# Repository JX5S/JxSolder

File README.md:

# Do not order the board, or blindly copy the design, there are several known issues. Namely:
- USB-PD doesn't work. I thought I could do dead battery the way I did, but it's not a good way to do it, use PA9 and PA10 instead
- Display reset needs to be wired via an RC filter to 3.3V
- Vref needs to be connected up
- Button logic is flipped - so DFU firmware upload doesn't work
- There are unidirectional transils on the input - which blow up when incorrect polarity is plugged in. Should be replaced by bidirectional transils, the ideal diodes will protect the input
- There aren't dedicated I2C pullups, which limits speed

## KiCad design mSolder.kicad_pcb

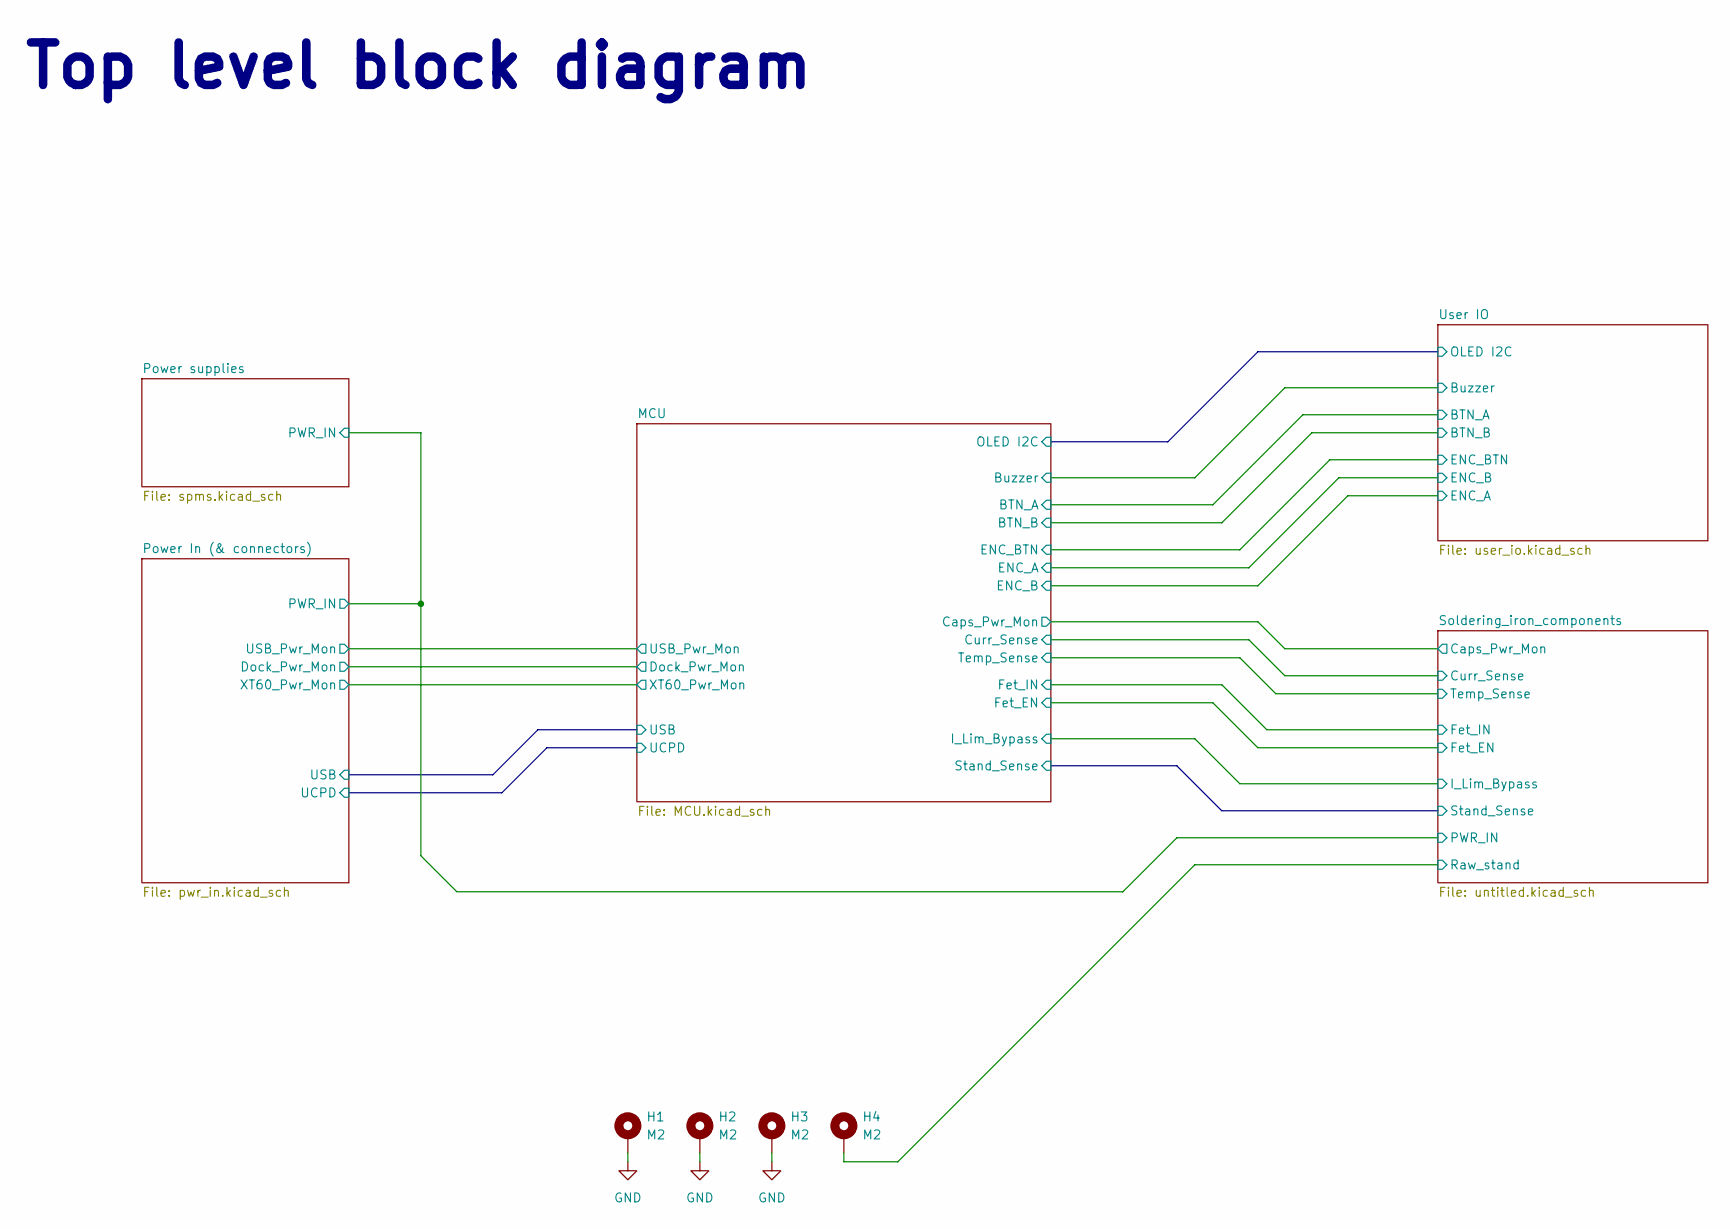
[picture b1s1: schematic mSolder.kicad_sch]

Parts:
H1, H2, H3, H4: M2; M2 solder nut; LCSC C3020134

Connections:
/Soldering_iron_components/Raw.Stand: H4.1; also elsewhere on the board
GND: H1.1, H2.1, H3.1; also elsewhere on the board

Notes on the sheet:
Top level block diagram

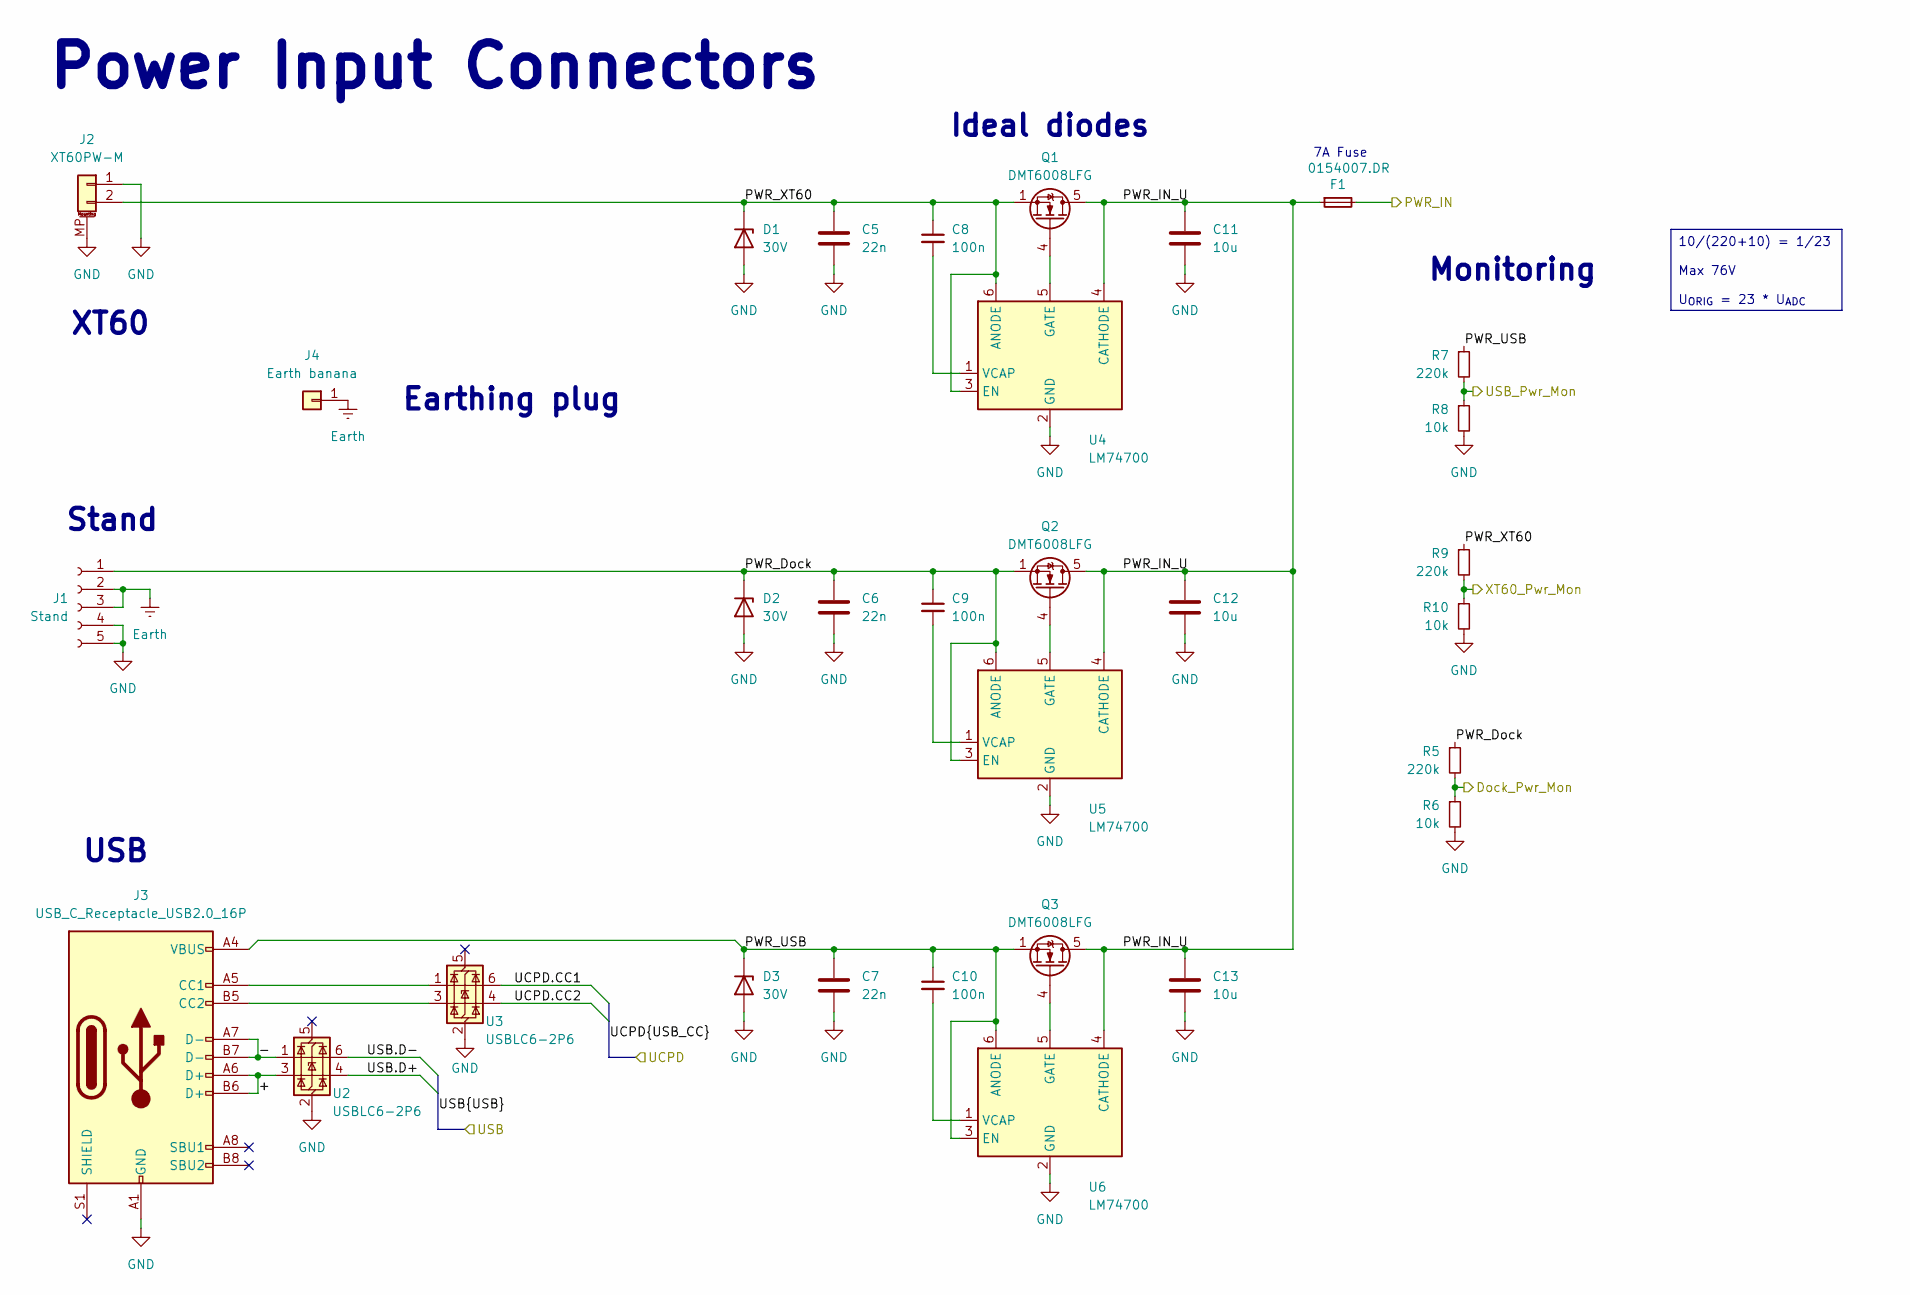
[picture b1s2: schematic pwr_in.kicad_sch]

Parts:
C5, C6, C7: 22n; C_0603_1608Metric; LCSC C21122
C8, C9, C10: 100n; C_0603_1608Metric; LCSC C1591
C11, C12, C13: 10u; C_1206_3216Metric; LCSC C13585
D1, D2, D3: 30V; D_SMA; LCSC C132943
F1: 0154007.DR; 0154100DR; Mouser Part Number 576-0154007.DR
J1: Stand; 1473969.1
J2: XT60PW-M; LCSC C98732
J3: USB_C_Receptacle_USB2.0_16P; USB_C_Receptacle_G-Switch_GT-USB-7010ASV; LCSC C963413
J4: Earth banana; CONN-TH_24.243.2; LCSC C7437324
Q1, Q2, Q3: DMT6008LFG; Diodes_PowerDI3333-8; LCSC C461111
R5, R7, R9: 220k; R_0603_1608Metric; LCSC C861231
R6, R8, R10: 10k; R_0603_1608Metric; LCSC C95204
U2, U3: USBLC6-2P6; SOT-666; LCSC C15999
U4, U5, U6: LM74700; SOT-23-6; LCSC C7589230

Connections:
/MCU/Dock_Pwr_Mon: R5.2, R6.1; also elsewhere on the board
/MCU/UCPD.CC1: U3.6 (I/O1); also elsewhere on the board
/MCU/UCPD.CC2: U3.4 (I/O2); also elsewhere on the board
/MCU/USB.D+: U2.4 (I/O2); also elsewhere on the board
/MCU/USB.D-: U2.6 (I/O1); also elsewhere on the board
/MCU/USB_Pwr_Mon: R7.2, R8.1; also elsewhere on the board
/MCU/XT60_Pwr_Mon: R9.2, R10.1; also elsewhere on the board
/Power In (& connectors)/+: J3.A6 (D+), J3.B6 (D+), U2.3 (I/O2)
/Power In (& connectors)/-: J3.A7 (D-), J3.B7 (D-), U2.1 (I/O1)
/Power In (& connectors)/PWR_Dock: C6.1, C9.1, D2.1 (K), J1.1, Q2.1 (S), Q2.2 (S), Q2.3 (S), R5.1, U5.3 (EN), U5.6 (ANODE)
/Power In (& connectors)/PWR_IN: F1.2; also elsewhere on the board
/Power In (& connectors)/PWR_IN_U: C11.1, C12.1, C13.1, F1.1, Q1.5 (D), Q2.5 (D), Q3.5 (D), U4.4 (CATHODE), U5.4 (CATHODE), U6.4 (CATHODE)
/Power In (& connectors)/PWR_USB: C7.1, C10.1, D3.1 (K), J3.A4 (VBUS), J3.A9 (VBUS), J3.B4 (VBUS), J3.B9 (VBUS), Q3.1 (S), Q3.2 (S), Q3.3 (S), R7.1, U6.3 (EN), U6.6 (ANODE)
/Power In (& connectors)/PWR_XT60: C5.1, C8.1, D1.1 (K), J2.2, Q1.1 (S), Q1.2 (S), Q1.3 (S), R9.1, U4.3 (EN), U4.6 (ANODE)
Earth: J1.2, J1.3, J4.1; also elsewhere on the board
GND: C5.2, C6.2, C7.2, C11.2, C12.2, C13.2, D1.2 (A), D2.2 (A), D3.2 (A), J1.4, J1.5, J2.1, J2.MP (MountPin), J3.A1 (GND), J3.A12 (GND), J3.B1 (GND), J3.B12 (GND), R6.2, R8.2, R10.2, U2.2 (GND), U3.2 (GND), U4.2 (GND), U5.2 (GND), U6.2 (GND); also elsewhere on the board
unnamed: J3.A5 (CC1), U3.1 (I/O1)
unnamed: J3.B5 (CC2), U3.3 (I/O2)
unnamed: Q1.4 (G), U4.5 (GATE)
unnamed: Q2.4 (G), U5.5 (GATE)
unnamed: Q3.4 (G), U6.5 (GATE)
unnamed: C8.2, U4.1 (VCAP)
unnamed: C9.2, U5.1 (VCAP)
unnamed: C10.2, U6.1 (VCAP)

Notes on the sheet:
Monitoring
Ideal diodes
Power Input Connectors
XT60
Earthing plug
USB
Stand
7A Fuse
10/(220+10) = 1/23 Max 76V U_{ORIG} = 23 * U_{ADC}

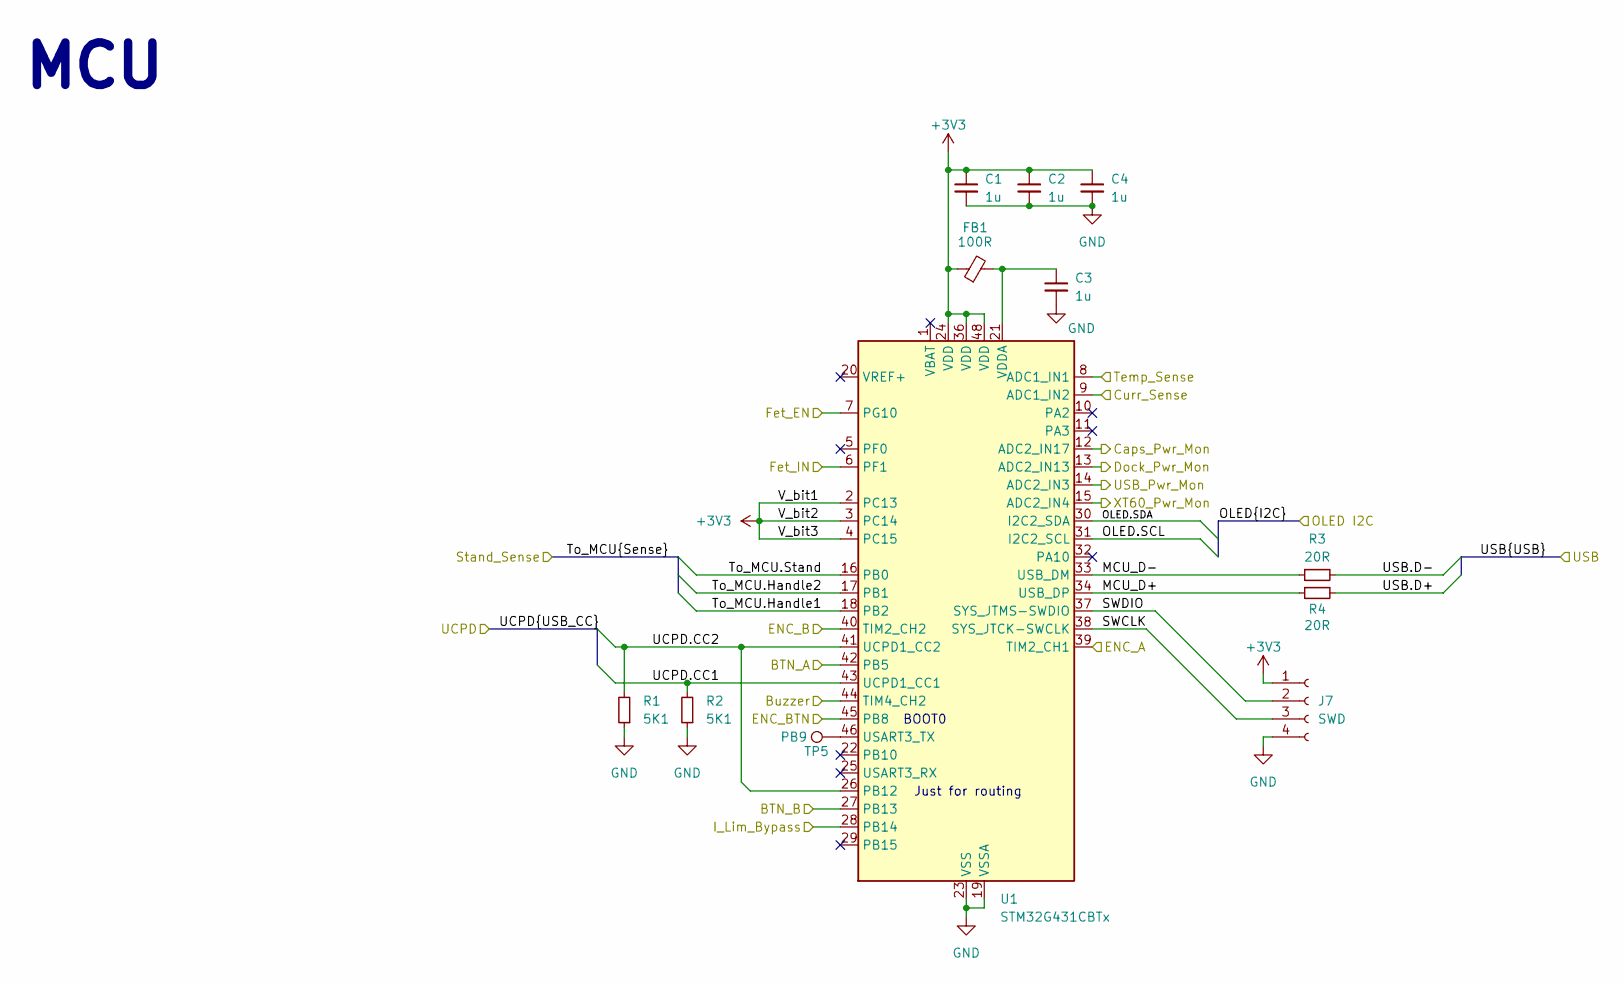
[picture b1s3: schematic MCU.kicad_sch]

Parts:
C1, C2, C3, C4: 1u; C_0603_1608Metric; LCSC C15849
FB1: 100R; R_0603_1608Metric; LCSC C107332
J7: SWD; PinHeader_1x04_P2.54mm_Vertical; LCSC C2691448
R1, R2: 5K1; R_0603_1608Metric; LCSC C105580
R3, R4: 20R; R_0603_1608Metric; LCSC C125758
TP5: PB9; TestPoint_Pad_D1.0mm
U1: STM32G431CBTx; LQFP-48_7x7mm_P0.5mm; LCSC C529355

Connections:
+3V3: C1.1, C2.1, C4.1, FB1.1, J7.1, U1.2 (PC13), U1.3 (PC14), U1.4 (PC15), U1.24 (VDD), U1.36 (VDD), U1.48 (VDD); also elsewhere on the board
/MCU/BTN_A: U1.42 (PB5); also elsewhere on the board
/MCU/BTN_B: U1.27 (PB13); also elsewhere on the board
/MCU/Buzzer: U1.44 (PB7); also elsewhere on the board
/MCU/Caps_Pwr_Mon: U1.12 (ADC2_IN17); also elsewhere on the board
/MCU/Curr_Sense: U1.9 (ADC1_IN2); also elsewhere on the board
/MCU/Dock_Pwr_Mon: U1.13 (ADC2_IN13); also elsewhere on the board
/MCU/ENC_A: U1.39 (TIM2_CH1); also elsewhere on the board
/MCU/ENC_B: U1.40 (TIM2_CH2); also elsewhere on the board
/MCU/ENC_BTN: U1.45 (PB8); also elsewhere on the board
/MCU/Fet_EN: U1.7 (PG10); also elsewhere on the board
/MCU/Fet_IN: U1.6 (PF1); also elsewhere on the board
/MCU/I_Lim_Bypass: U1.28 (PB14); also elsewhere on the board
/MCU/MCU_D+: R4.1, U1.34 (USB_DP)
/MCU/MCU_D-: R3.1, U1.33 (USB_DM)
/MCU/OLED.SCL: U1.31 (I2C2_SCL); also elsewhere on the board
/MCU/OLED.SDA: U1.30 (I2C2_SDA); also elsewhere on the board
/MCU/SWCLK: J7.3, U1.38 (SYS_JTCK-SWCLK)
/MCU/SWDIO: J7.2, U1.37 (SYS_JTMS-SWDIO)
/MCU/Temp_Sense: U1.8 (ADC1_IN1); also elsewhere on the board
/MCU/To_MCU.Handle1: U1.18 (PB2); also elsewhere on the board
/MCU/To_MCU.Handle2: U1.17 (PB1); also elsewhere on the board
/MCU/To_MCU.Stand: U1.16 (PB0); also elsewhere on the board
/MCU/UCPD.CC1: R2.2, U1.43 (UCPD1_CC1); also elsewhere on the board
/MCU/UCPD.CC2: R1.2, U1.26 (PB12), U1.41 (UCPD1_CC2); also elsewhere on the board
/MCU/USB.D+: R4.2; also elsewhere on the board
/MCU/USB.D-: R3.2; also elsewhere on the board
/MCU/USB_Pwr_Mon: U1.14 (ADC2_IN3); also elsewhere on the board
/MCU/XT60_Pwr_Mon: U1.15 (ADC2_IN4); also elsewhere on the board
GND: C1.2, C2.2, C3.2, C4.2, J7.4, R1.1, R2.1, U1.19 (VSSA), U1.23 (VSS), U1.35 (VSS), U1.47 (VSS); also elsewhere on the board
unnamed: TP5.1, U1.46 (USART3_TX)
unnamed: C3.1, FB1.2, U1.21 (VDDA)

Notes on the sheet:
BOOT0
Just for routing
MCU

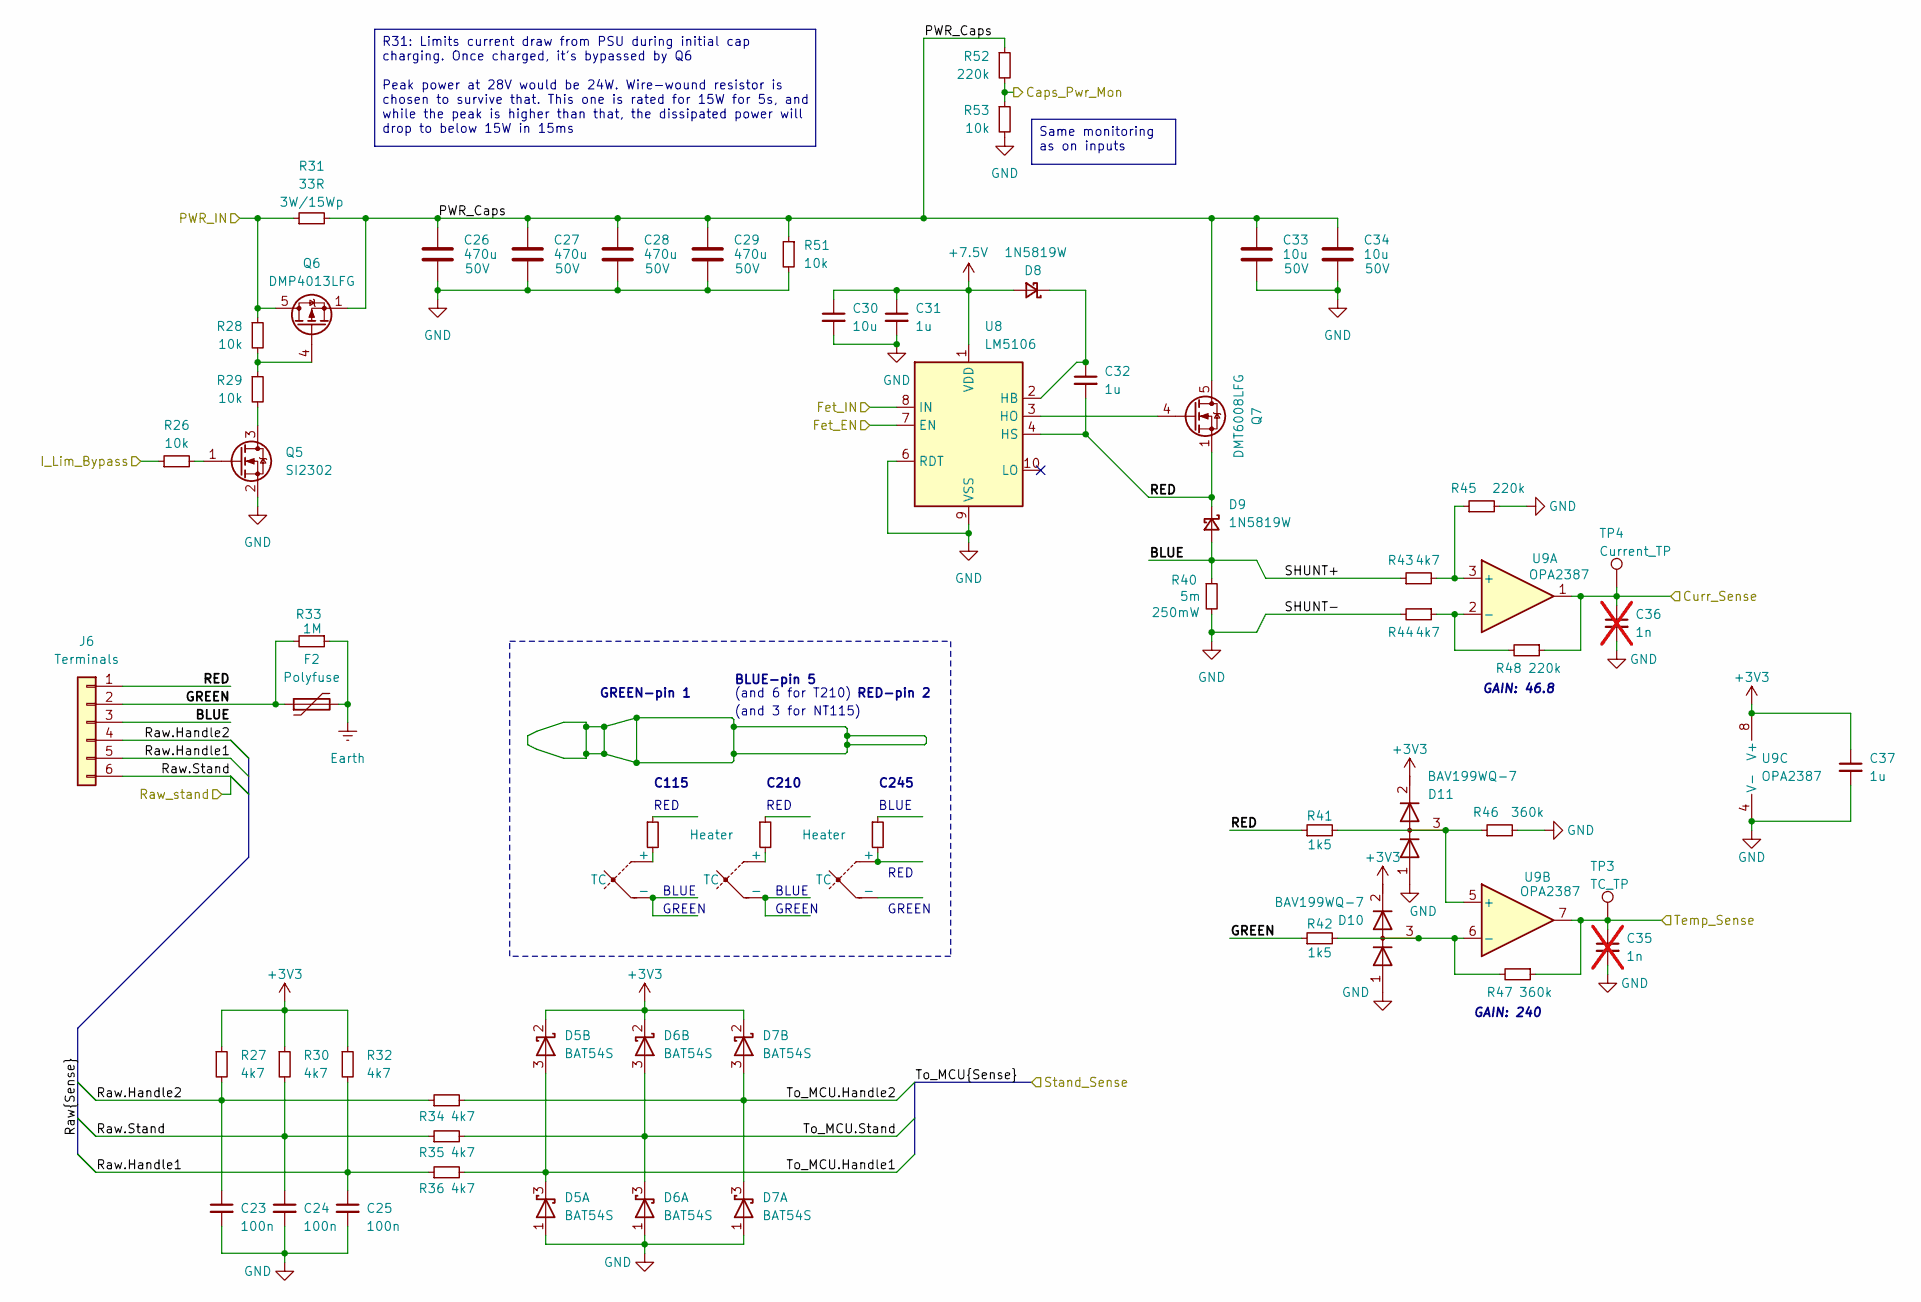
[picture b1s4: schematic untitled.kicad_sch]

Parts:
C23, C24, C25: 100n; C_0603_1608Metric; Manufacturer_Part_Number C0603C104J5RACTU; Mouser Part Number 80-C0603C104J5R
C26, C27, C28, C29: 470u; CP_Radial_D12.5mm_P5.00mm_L20_Laid on side; Voltage 50V; LCSC C1586027
C30: 10u; C_1206_3216Metric; LCSC C13585
C31, C32, C37: 1u; C_0603_1608Metric; LCSC C15849
C33, C34: 10u; C_1210_3225Metric; Voltage 50V; LCSC C126612
C35, C36: 1n; C_0603_1608Metric; Manufacturer_Part_Number C0603C102K3GAC; Mouser Part Number 80-C0603C102K3G; not fitted
D5, D6, D7: BAT54S; SOT-23; LCSC C47546
D8, D9: 1N5819W; D_SOD-123; LCSC C727115
D10, D11: BAV199WQ-7; SOT-323_SC-70; Mouser Part Number 621-BAV199WQ-7
F2: Polyfuse; Fuse_2512_6332Metric; LCSC C41364424
J6: Terminals; screw_terminal_6x3.81; LCSC C5143696
Q5: SI2302; TSOT-23; LCSC C5310967
Q6: DMP4013LFG; Diodes_PowerDI3333-8; LCSC C460203
Q7: DMT6008LFG; Diodes_PowerDI3333-8; LCSC C461111
R26, R28, R29, R51, R53: 10k; R_0603_1608Metric; LCSC C95204
R27, R30, R32, R34, R35, R36, R43, R44: 4k7; R_0603_1608Metric; Manufacturer_Part_Number ERJ-3RBD4701V; Mouser Part Number 667-ERJ-3RBD4701V
R31: 33R; R_TyOHM_SMW_3W; LCSC C2937341
R33: 1M; R_2512_6332Metric; LCSC C276335
R37, R38: Heater
R39: Heater 2 OHM
R40: 5m; R_1206_3216Metric; LCSC C875583
R41, R42: 1k5; R_0603_1608Metric; Manufacturer_Part_Number ERJ-H3ED1501V; Mouser Part Number 667-ERJ-H3ED1501V
R45, R48: 220k; R_0603_1608Metric; Manufacturer_Part_Number ERJ-3RED2203V; Mouser Part Number 667-ERJ-3RED2203V
R46, R47: 360k; R_0603_1608Metric; Manufacturer_Part_Number ERJ-3RED3603V; Mouser Part Number 667-ERJ-3RED3603V
R52: 220k; R_0603_1608Metric; LCSC C861231
TC1, TC2, TC3: TC
TP3: TC_TP; TestPoint_Pad_D1.0mm
TP4: Current_TP; TestPoint_Pad_D1.0mm
U8: LM5106; VSSOP-10_3x3mm_P0.5mm; LCSC C91879
U9: OPA2387; VSSOP-8_3x3mm_P0.65mm; LCSC C2861203

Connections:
+3V3: C37.1, D5.2 (K), D6.2 (K), D7.2 (K), D10.2, D11.2, R27.1, R30.1, R32.1, U9.8 (V+); also elsewhere on the board
+7.5V: C30.1, C31.1, D8.2 (A), U8.1 (VDD); also elsewhere on the board
/MCU/Caps_Pwr_Mon: R52.2, R53.1; also elsewhere on the board
/MCU/Curr_Sense: C36.1, R48.1, TP4.1, U9.1; also elsewhere on the board
/MCU/Fet_EN: U8.7 (EN); also elsewhere on the board
/MCU/Fet_IN: U8.8 (IN); also elsewhere on the board
/MCU/I_Lim_Bypass: R26.1; also elsewhere on the board
/MCU/Temp_Sense: C35.1, R47.1, TP3.1, U9.7; also elsewhere on the board
/MCU/To_MCU.Handle1: D5.3 (K), R36.2; also elsewhere on the board
/MCU/To_MCU.Handle2: D7.3 (K), R34.2; also elsewhere on the board
/MCU/To_MCU.Stand: D6.3 (K), R35.2; also elsewhere on the board
/Power In (& connectors)/PWR_IN: Q6.5 (D), R28.1, R31.1; also elsewhere on the board
/Soldering_iron_components/BLUE: D9.2 (A), J6.3, R40.1, R43.1
/Soldering_iron_components/GREEN: F2.1, J6.2, R33.2, R42.1
/Soldering_iron_components/PWR_Caps: C26.1, C27.1, C28.1, C29.1, C33.1, C34.1, Q6.1 (S), Q6.2 (S), Q6.3 (S), Q7.5 (D), R31.2, R51.1, R52.1
/Soldering_iron_components/RED: C32.2, D9.1 (K), J6.1, Q7.1 (S), Q7.2 (S), Q7.3 (S), R41.1, U8.4 (HS)
/Soldering_iron_components/Raw.Handle1: C25.1, J6.5, R32.2, R36.1
/Soldering_iron_components/Raw.Handle2: C23.1, J6.4, R27.2, R34.1
/Soldering_iron_components/Raw.Stand: C24.1, J6.6, R30.2, R35.1; also elsewhere on the board
Earth: F2.2, R33.1; also elsewhere on the board
GND: C23.2, C24.2, C25.2, C26.2, C27.2, C28.2, C29.2, C30.2, C31.2, C33.2, C34.2, C35.2, C36.2, C37.2, D5.1 (A), D6.1 (A), D7.1 (A), D10.1, D11.1, Q5.2 (S), R40.2, R44.2, R45.2, R46.2, R51.2, R53.2, U8.6 (RDT), U8.9 (VSS), U9.4 (V-); also elsewhere on the board
unnamed: C32.1, D8.1 (K), U8.2 (HB)
unnamed: Q5.3 (D), R29.2
unnamed: Q5.1 (G), R26.2
unnamed: Q6.4 (G), R28.2, R29.1
unnamed: Q7.4 (G), U8.3 (HO)
unnamed: R37.2, TC1.1 (+)
unnamed: R38.2, TC2.1 (+)
unnamed: R39.2, TC3.1 (+)
unnamed: R43.2, R45.1, U9.3 (+)
unnamed: R44.1, R48.2, U9.2 (-)
unnamed: D11.3, R41.2, R46.1, U9.5 (+)
unnamed: D10.3, R42.2, R47.2, U9.6 (-)

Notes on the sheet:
BLUE
RED-pin 2
BLUE-pin 5
C245
GREEN
(and 3 for NT115)
GAIN: 240
RED
GREEN-pin 1
RED
GAIN: 46.8
C210
C115
(and 6 for T210)
Same monitoring as on inputs
R31: Limits current draw from PSU during initial cap charging. Once charged, it's bypassed by Q6 Peak power at 28V would be 24W. Wire-wound resistor is chosen to survive that. This one is rated for 15W for 5s, and while the peak is higher than that, the dissipated power will drop to below 15W in 15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

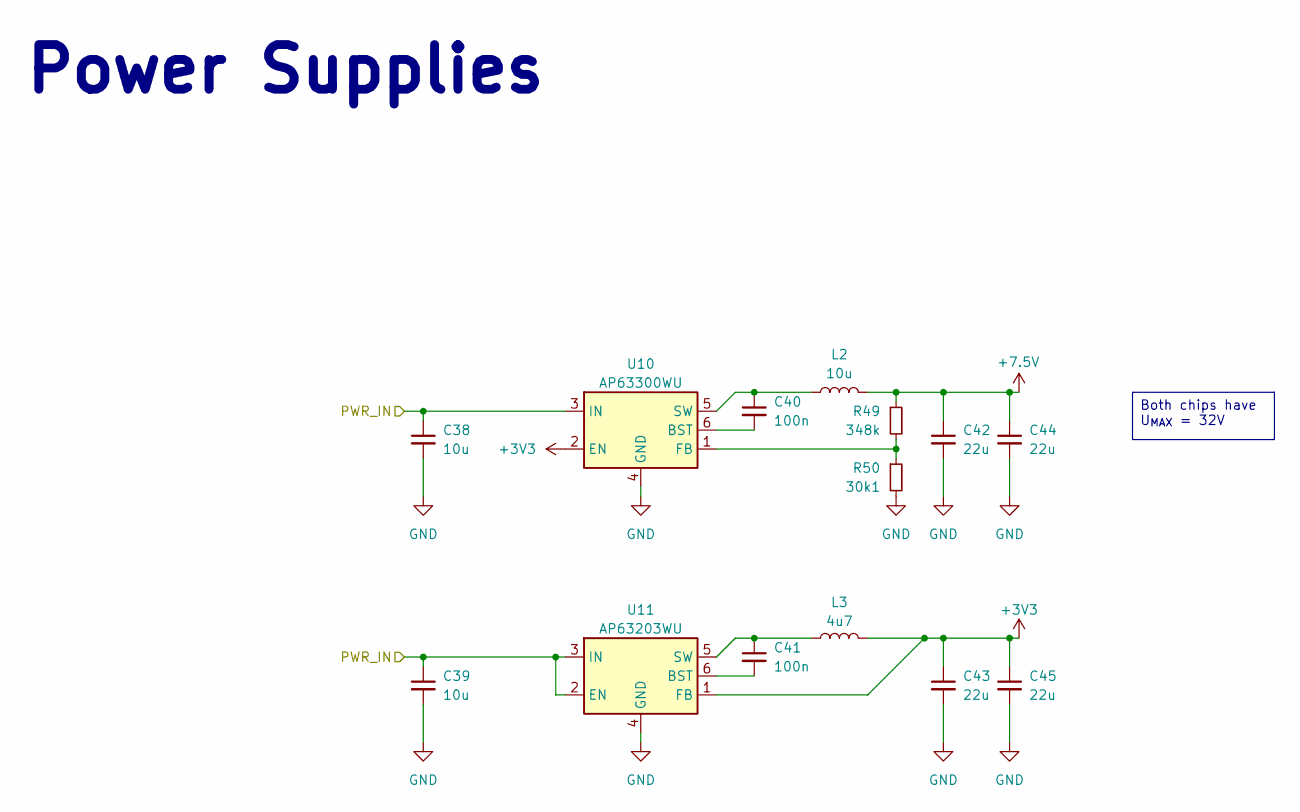
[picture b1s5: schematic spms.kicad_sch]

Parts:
C38, C39: 10u; C_1206_3216Metric; LCSC C13585
C40, C41: 100n; C_0603_1608Metric; LCSC C1591
C42, C43, C44, C45: 22u; C_1206_3216Metric; LCSC C77091
L2: 10u; L_Chilisin_BMRA00040420; LCSC C177242
L3: 4u7; L_Chilisin_BMRA00040420; LCSC C167208
R49: 348k; R_0603_1608Metric; LCSC C227828
R50: 30k1; R_0603_1608Metric; LCSC C137745
U10: AP63300WU; TSOT-23-6; LCSC C2158012
U11: AP63203WU; TSOT-23-6; LCSC C780769

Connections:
+3V3: C43.1, C45.1, L3.2, U10.2 (EN), U11.1 (FB); also elsewhere on the board
+7.5V: C42.1, C44.1, L2.2, R49.1; also elsewhere on the board
/Power In (& connectors)/PWR_IN: C38.1, C39.1, U10.3 (IN), U11.2 (EN), U11.3 (IN); also elsewhere on the board
GND: C38.2, C39.2, C42.2, C43.2, C44.2, C45.2, R50.2, U10.4 (GND), U11.4 (GND); also elsewhere on the board
unnamed: C40.2, U10.6 (BST)
unnamed: R49.2, R50.1, U10.1 (FB)
unnamed: C40.1, L2.1, U10.5 (SW)
unnamed: C41.2, U11.6 (BST)
unnamed: C41.1, L3.1, U11.5 (SW)

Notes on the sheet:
Power Supplies
Both chips have U_{MAX} = 32V

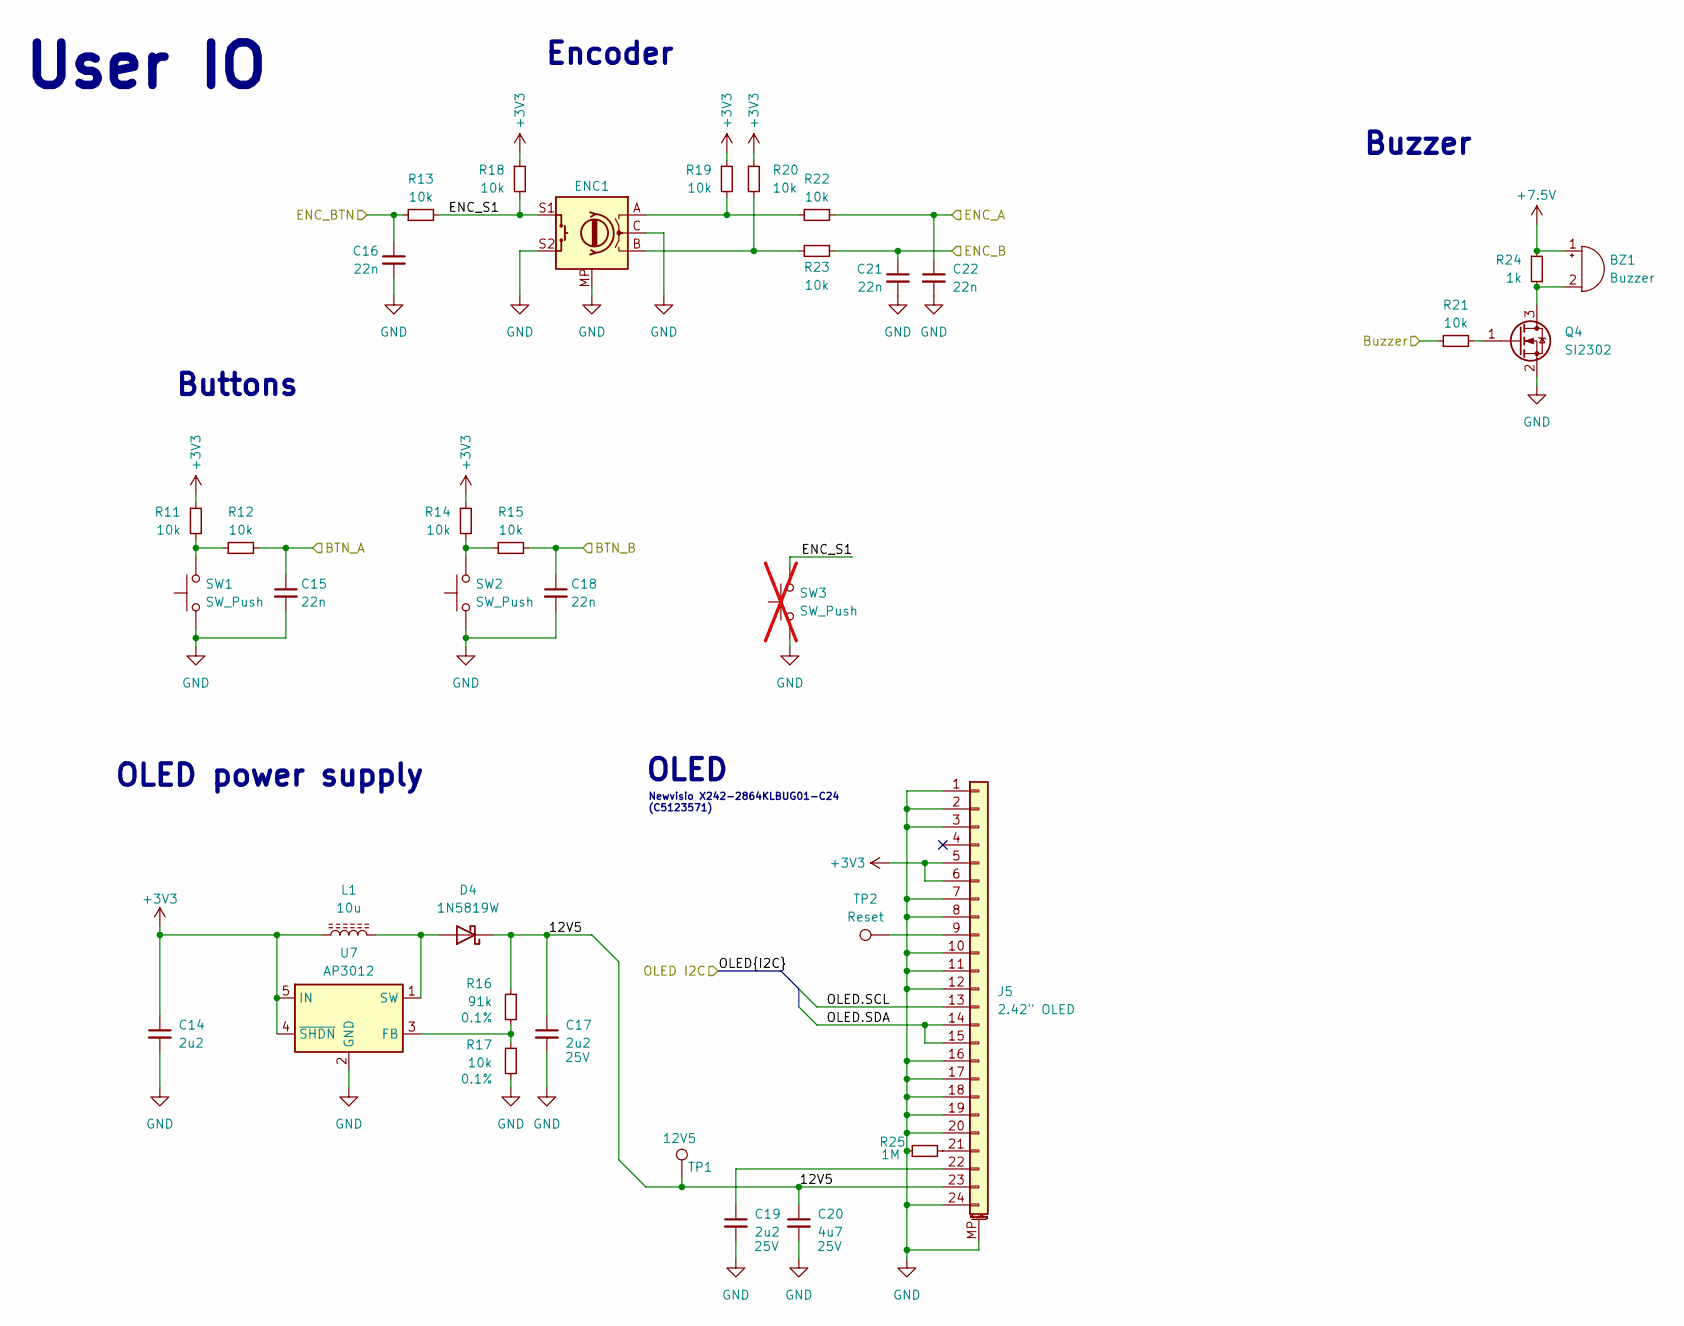
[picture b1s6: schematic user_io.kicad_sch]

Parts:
BZ1: Buzzer; Buzzer_Murata_PKMCS0909E; LCSC C910763
C14: 2u2; C_0603_1608Metric; LCSC C57895
C15, C16, C18, C21, C22: 22n; C_0603_1608Metric; LCSC C21122
C17, C19: 2u2; C_0603_1608Metric; Voltage 25V; LCSC C57895
C20: 4u7; C_0603_1608Metric; Voltage 25V; LCSC C69335
D4: 1N5819W; D_SOD-123; LCSC C727115
ENC1: RotaryEncoder_Switch_MP; RotaryEncoder_Bourns_Vertical_PEC12R-3x17F-Sxxxx; LCSC C143801
J5: 2.42" OLED; Jushuo_AFC07-S24FCA-00_1x24-1MP_P0.50_Horizontal; LCSC C262567
L1: 10u; L_1206_3216Metric; LCSC C281117
Q4: SI2302; TSOT-23; LCSC C5310967
R11, R12, R13, R14, R15, R18, R19, R20, R21, R22, R23: 10k; R_0603_1608Metric; LCSC C95204
R16: 91k; R_0603_1608Metric; Tolerance 0.1%; LCSC C326721
R17: 10k; R_0603_1608Metric; Tolerance 0.1%; LCSC C95204
R24: 1k; R_0603_1608Metric; LCSC C22548
R25: 1M; R_0603_1608Metric; LCSC C105578
SW1, SW2: SW_Push; Switch_ALPSALPINE_SKPMAME010; LCSC C115350
SW3: SW_Push; Switch_ALPSALPINE_SKPMAME010; LCSC C115350; not fitted
TP1: 12V5; TestPoint_Pad_D1.0mm
TP2: Reset; TestPoint_Pad_D1.0mm
U7: AP3012; SOT-23-5; LCSC C102618

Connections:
+3V3: C14.1, J5.5, J5.6, L1.1, R11.1, R14.1, R18.1, R19.1, R20.1, U7.4 (~SHDN), U7.5 (IN); also elsewhere on the board
+7.5V: BZ1.1 (+), R24.1; also elsewhere on the board
/MCU/BTN_A: C15.1, R12.2; also elsewhere on the board
/MCU/BTN_B: C18.1, R15.2; also elsewhere on the board
/MCU/Buzzer: R21.1; also elsewhere on the board
/MCU/ENC_A: C21.1, R23.1; also elsewhere on the board
/MCU/ENC_B: C22.1, R22.1; also elsewhere on the board
/MCU/ENC_BTN: C16.1, R13.1; also elsewhere on the board
/MCU/OLED.SCL: J5.13; also elsewhere on the board
/MCU/OLED.SDA: J5.14, J5.15; also elsewhere on the board
/User IO/12V5: C17.1, C20.1, D4.1 (K), J5.23, R16.1, TP1.1
/User IO/ENC_S1: ENC1.S1, R13.2, R18.2, SW3.2
GND: C14.2, C15.2, C16.2, C17.2, C18.2, C19.2, C20.2, C21.2, C22.2, ENC1.C, ENC1.MP, ENC1.S2, J5.1, J5.2, J5.3, J5.7, J5.8, J5.10, J5.11, J5.12, J5.16, J5.17, J5.18, J5.19, J5.20, J5.24, J5.MP (MountPin), Q4.2 (S), R17.2, R25.1, SW1.1, SW2.1, SW3.1, U7.2 (GND); also elsewhere on the board
unnamed: BZ1.2 (-), Q4.3 (D), R24.2
unnamed: D4.2 (A), L1.2, U7.1 (SW)
unnamed: ENC1.A, R19.2, R22.2
unnamed: ENC1.B, R20.2, R23.2
unnamed: J5.9, TP2.1
unnamed: J5.21, R25.2
unnamed: C19.1, J5.22
unnamed: Q4.1 (G), R21.2
unnamed: R11.2, R12.1, SW1.2
unnamed: R14.2, R15.1, SW2.2
unnamed: R16.2, R17.1, U7.3 (FB)

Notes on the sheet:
Encoder
OLED power supply
User IO
OLED
Buttons
Newvisio X242-2864KLBUG01-C24 (C5123571)
Buzzer

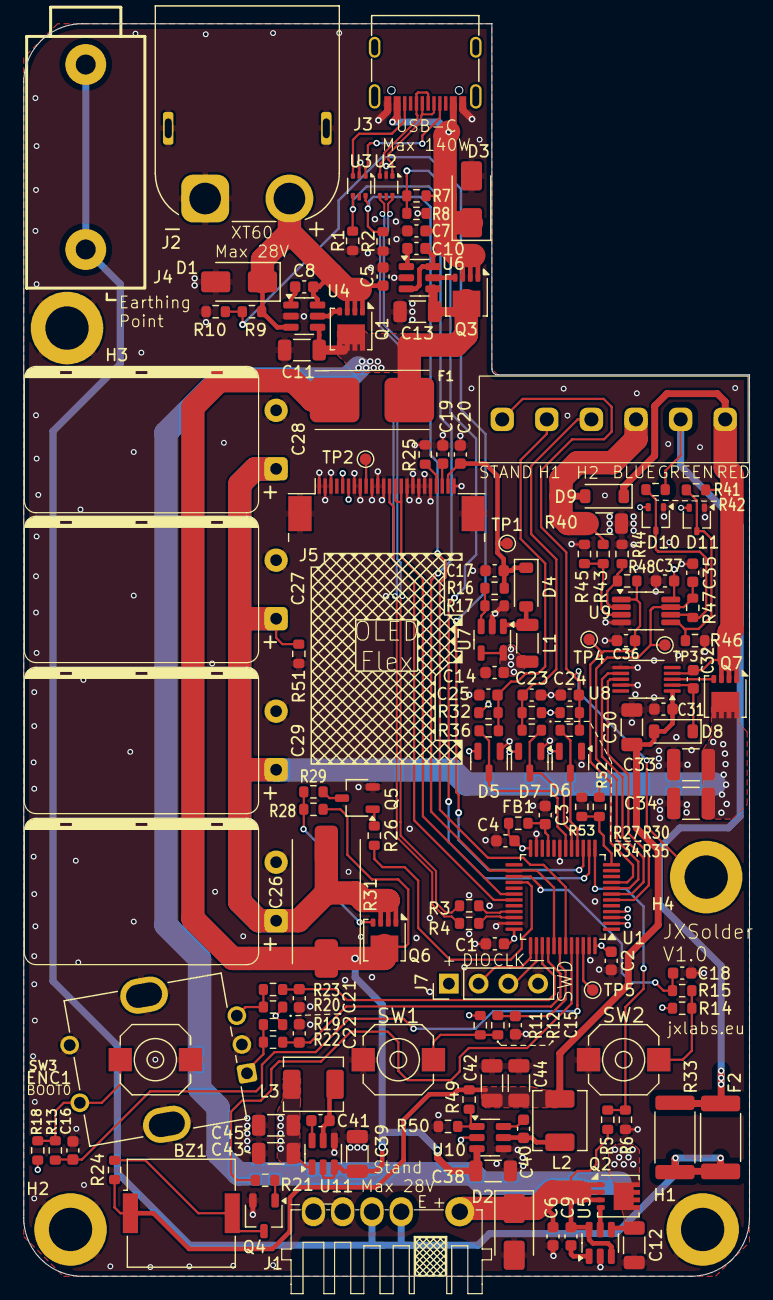
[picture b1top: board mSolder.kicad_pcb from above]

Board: 4 copper layers, 62.0 x 107.0 mm, 152 parts (1 on the bottom side), 83 nets.

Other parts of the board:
QR*****: https://github.com/JX5S/jxsolder; QR_Github_Inverted

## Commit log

2025-03-01 Added files of original version for viewing
2025-03-01 Added schematic PDF
